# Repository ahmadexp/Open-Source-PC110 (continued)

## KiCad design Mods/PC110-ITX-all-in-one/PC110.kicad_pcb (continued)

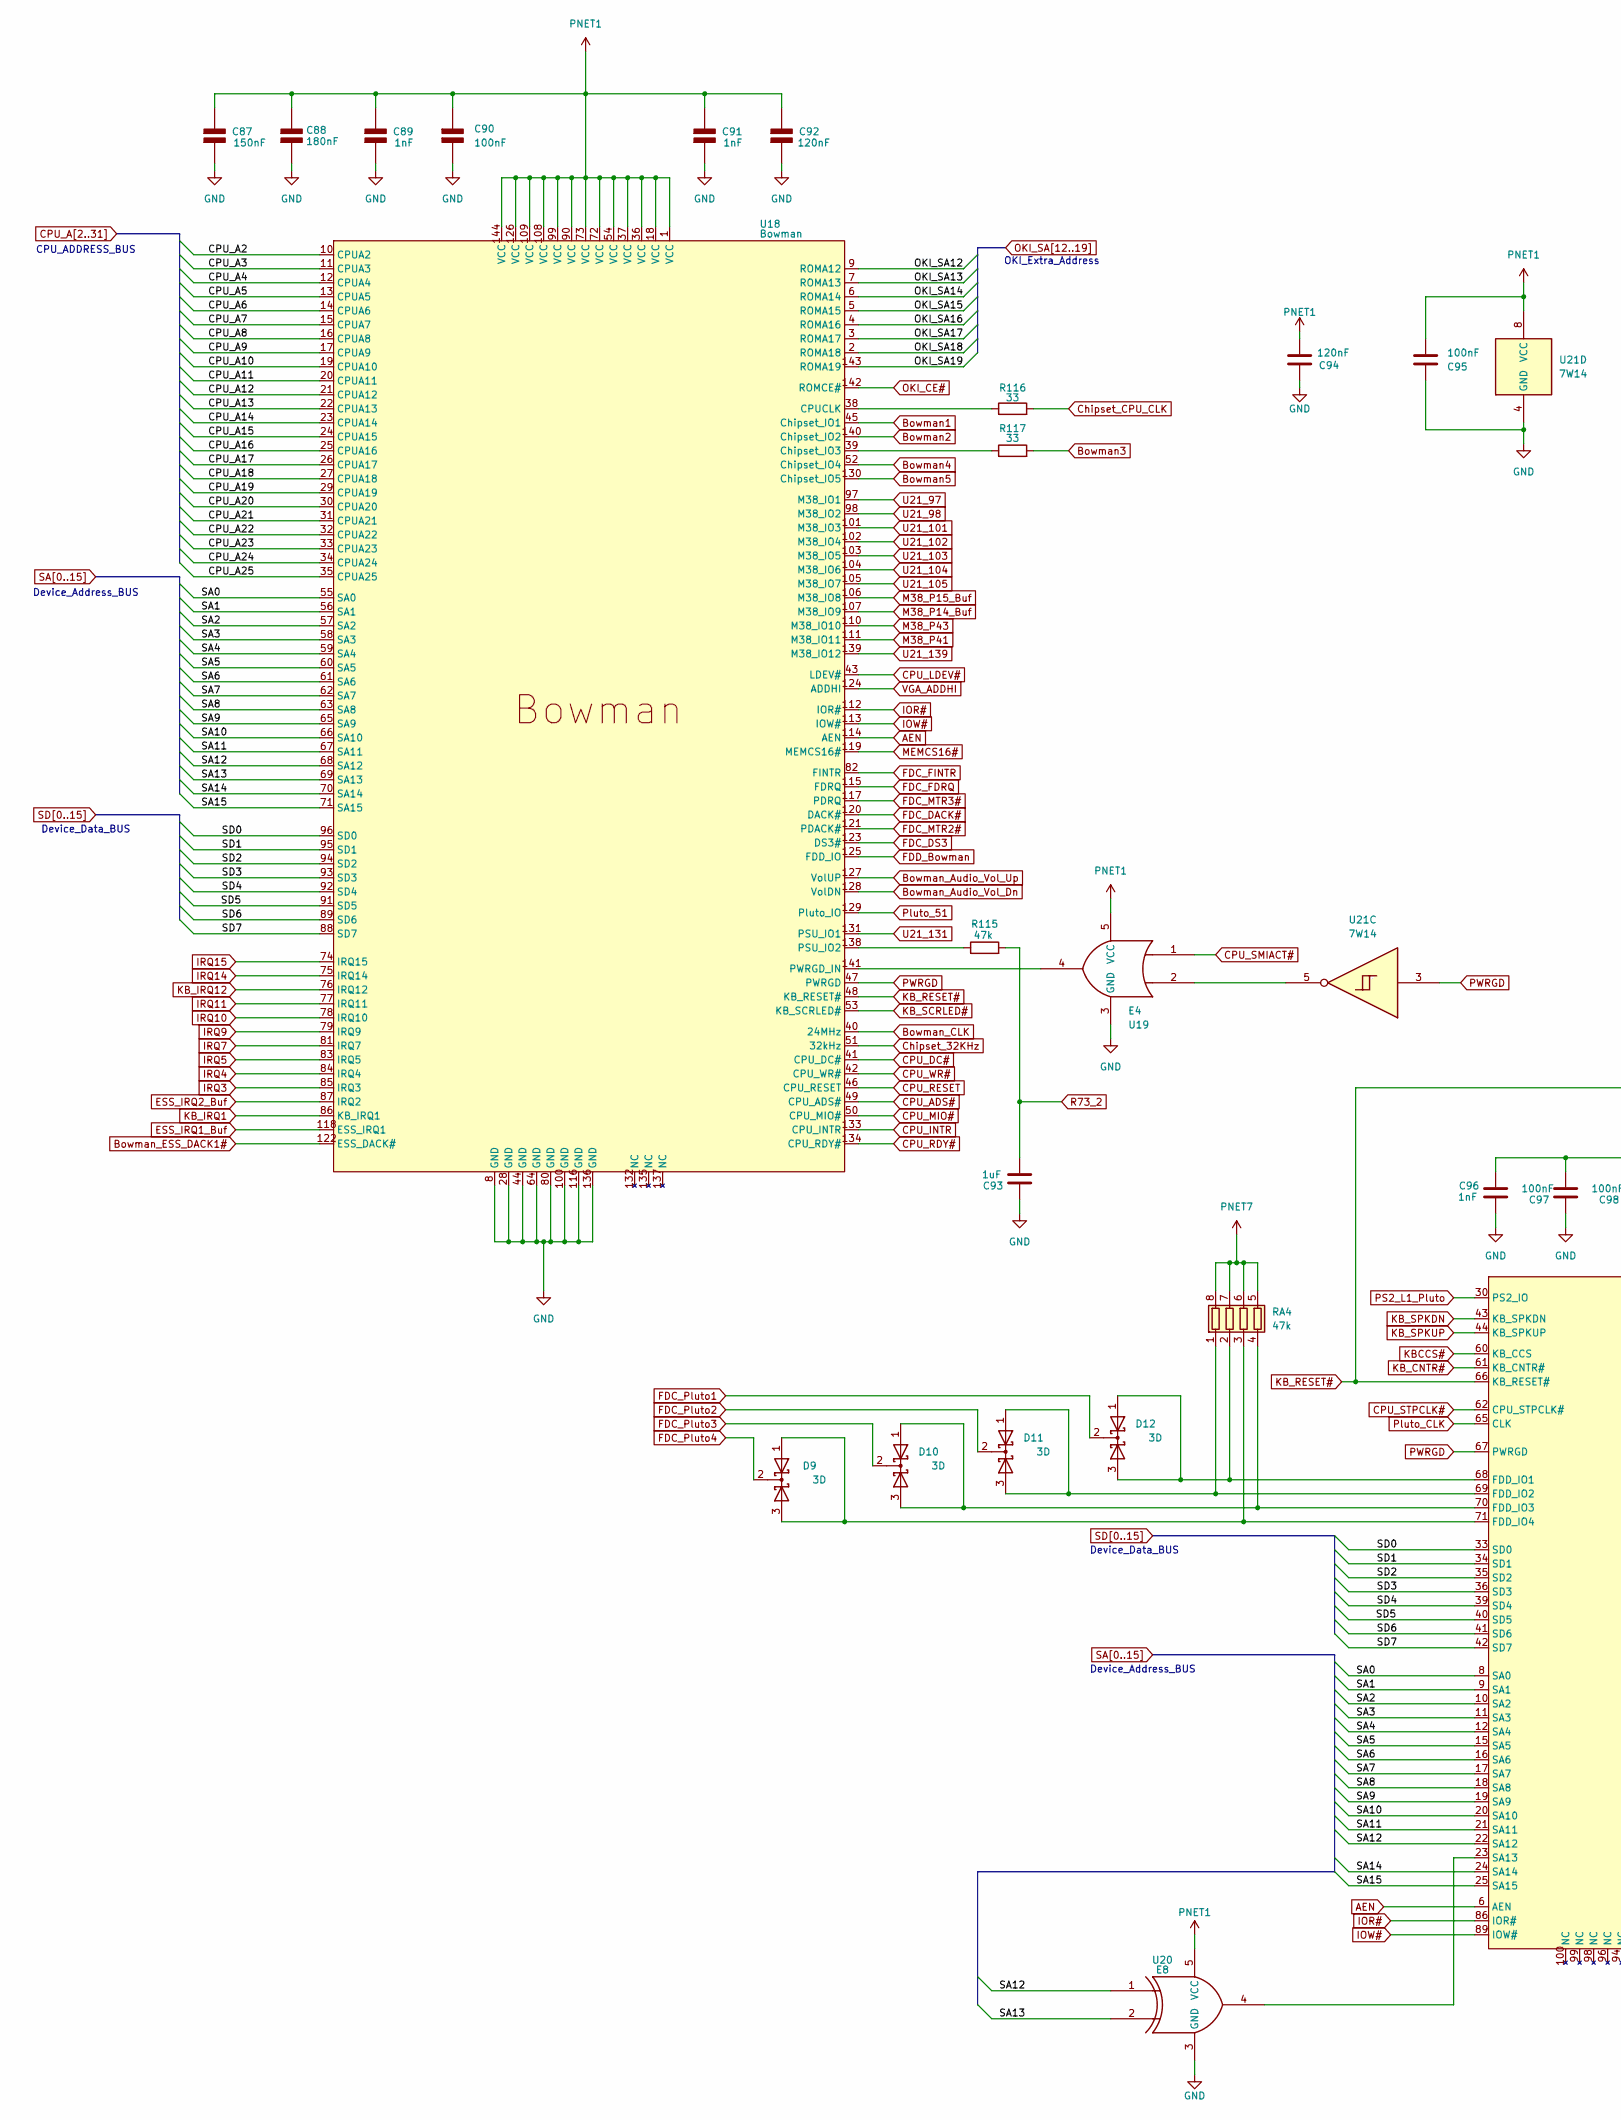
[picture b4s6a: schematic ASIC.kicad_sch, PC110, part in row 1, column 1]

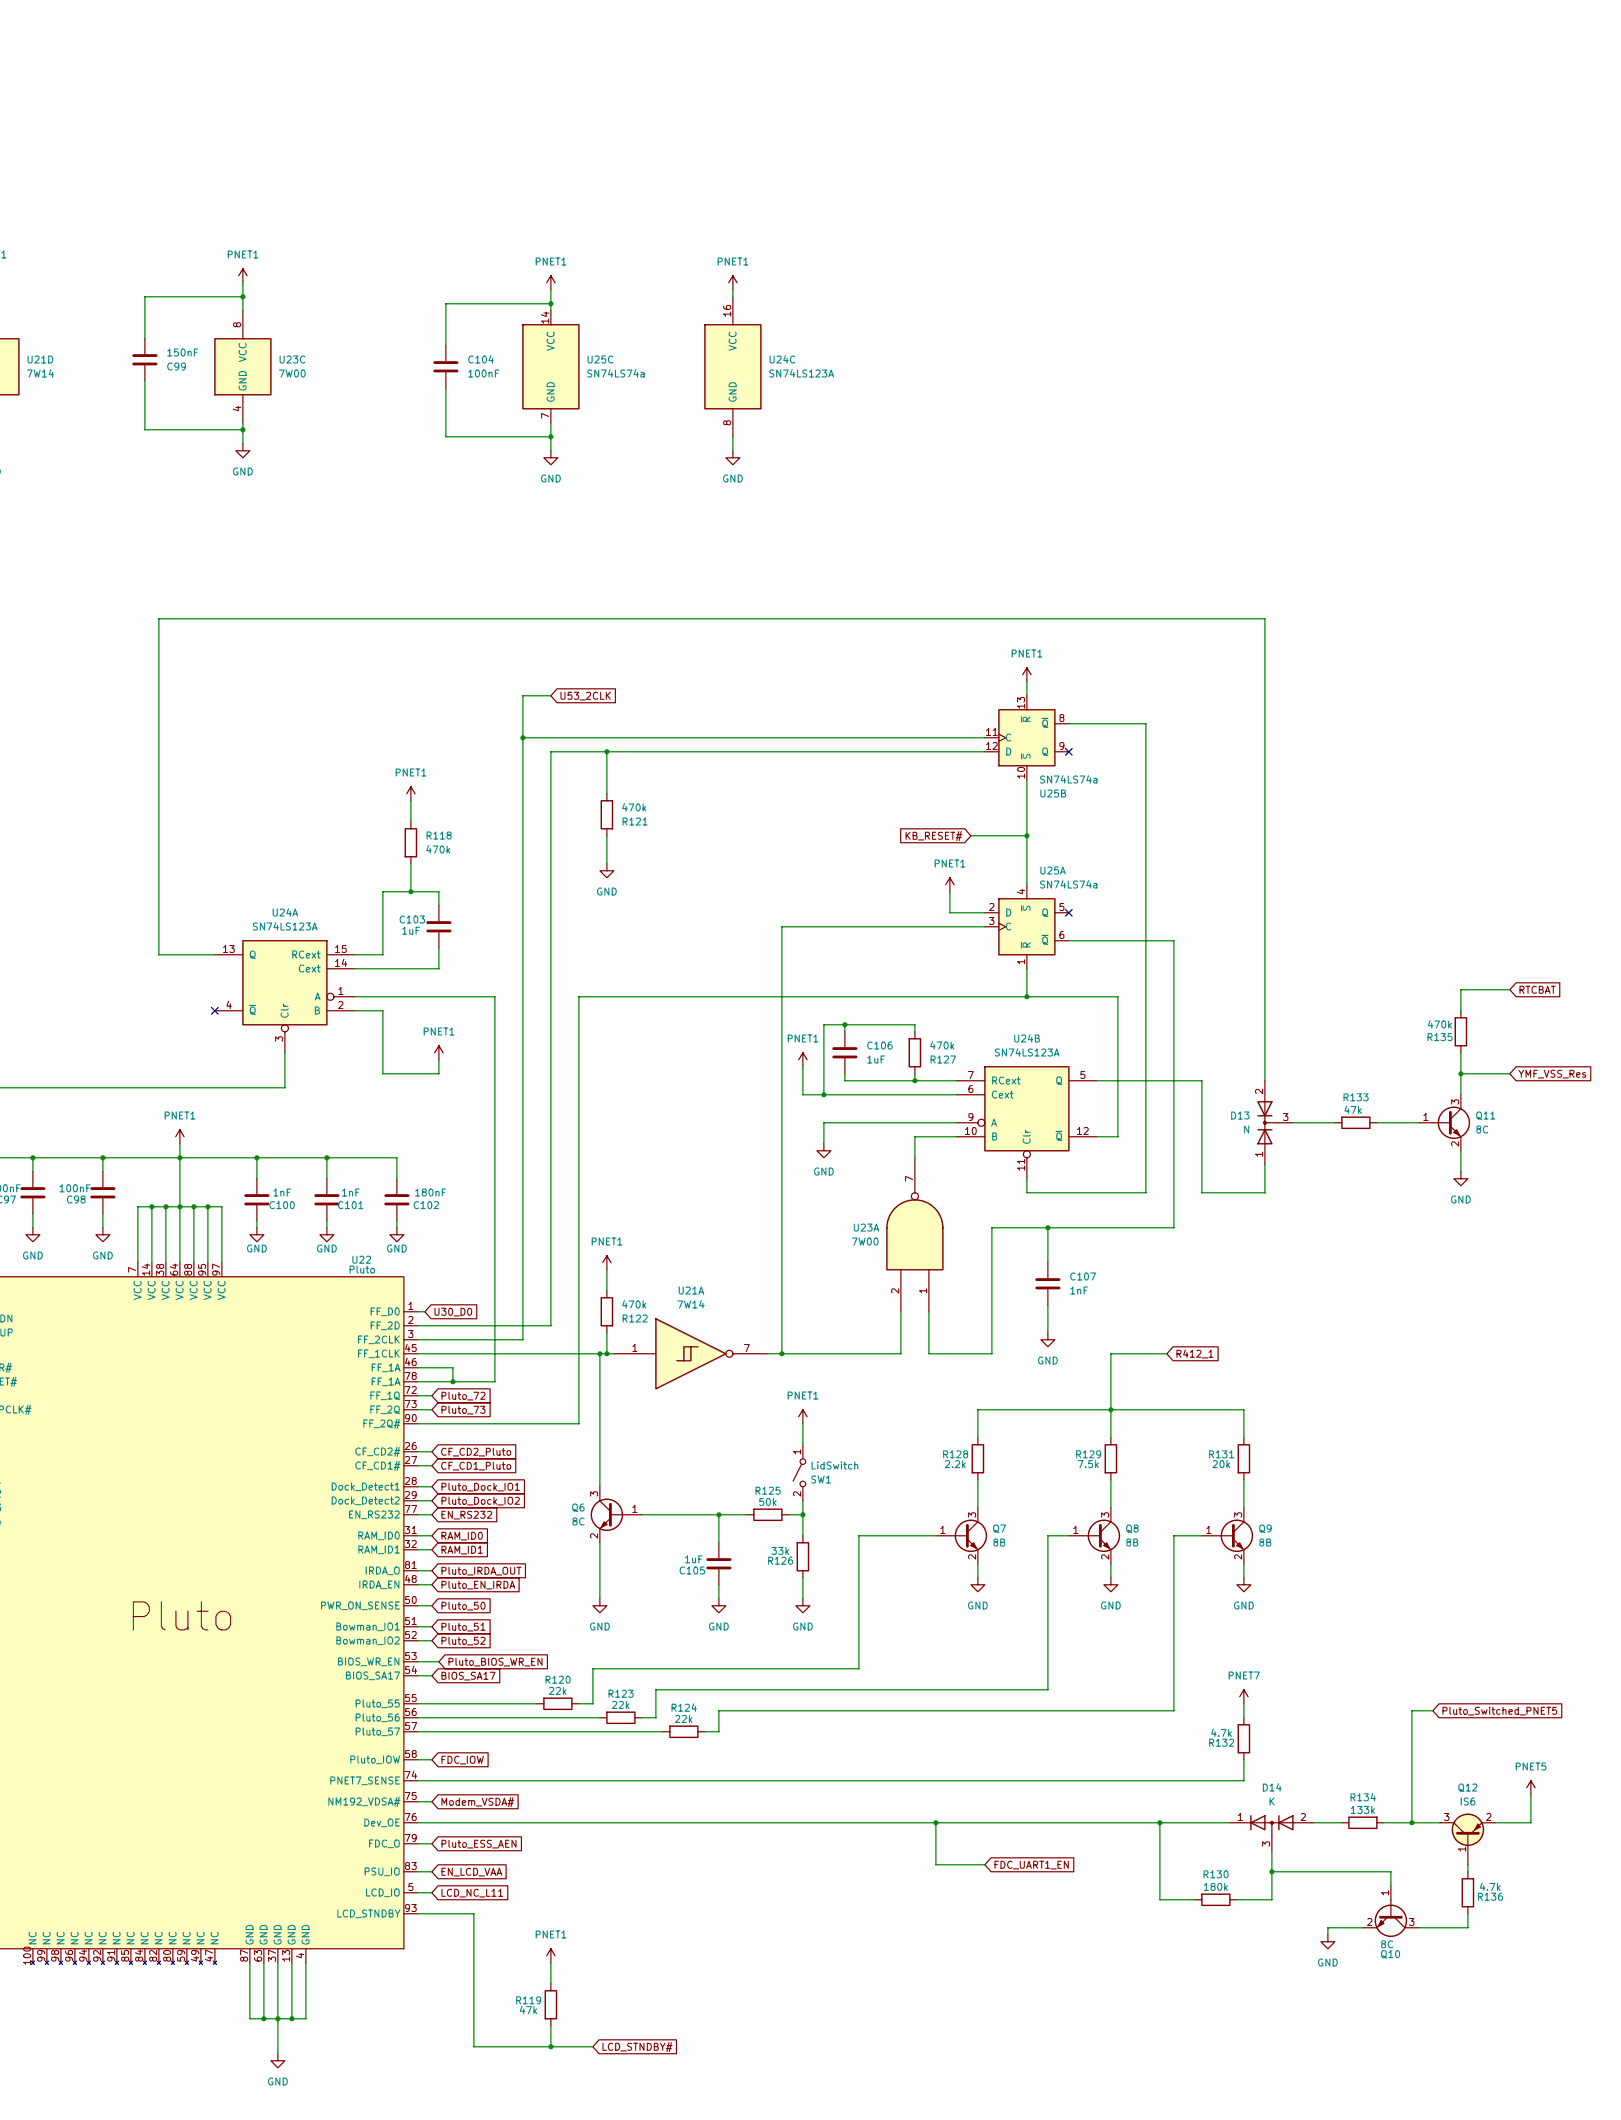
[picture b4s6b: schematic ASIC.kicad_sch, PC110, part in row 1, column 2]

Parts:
C87, C99: 150nF; C_0402_1005Metric
C88, C102: 180nF; C_0402_1005Metric
C89, C91, C96, C100, C101, C107: 1nF; C_0402_1005Metric
C90, C95, C97, C98, C104: 100nF; C_0402_1005Metric
C92, C94: 120nF; C_0402_1005Metric
C93, C103, C105, C106: 1uF; C_0603_1608Metric
D9, D10, D11, D12: 3D
D13: N; SOT-416
D14: K; SOT-416L
Q6, Q10, Q11: 8C; SOT-416
Q7, Q8: 8B; SOT-523
Q9: 8B; SOT-416
Q12: IS6; TSOT-23
R115, R119, R133: 47k; R_0402_1005Metric
R116, R117: 33; R_0402_1005Metric
R118, R121, R122, R127, R135: 470k; R_0402_1005Metric
R120, R123, R124: 22k; R_0402_1005Metric
R125: 50k; R_0402_1005Metric
R126: 33k; R_0402_1005Metric
R128: 2.2k; R_0402_1005Metric
R129: 7.5k; R_0402_1005Metric
R130: 180k; R_0402_1005Metric
R131: 20k; R_0402_1005Metric
R132, R136: 4.7k; R_0402_1005Metric
R134: 133k; R_0402_1005Metric
RA4: 47k; R-array
SW1: LidSwitch
U18: Bowman
U19: E4; SOT-353
U20: E8; SOT-353
U21: 7W14; sso-8
U22: Pluto
U23: 7W00; sso-8
U24: SN74LS123A; TSSOP-16_4.4x5mm_P0.65mm
U25: SN74LS74a; TSSOP-14_4.4x5mm_P0.65mm

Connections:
AEN: U18.114 (AEN), U22.6 (AEN); also elsewhere on the board
BIOS_SA17: U22.54 (BIOS_SA17); also elsewhere on the board
Bowman1: U18.45 (Chipset_IO1); also elsewhere on the board
Bowman2: U18.140 (Chipset_IO2); also elsewhere on the board
Bowman3: R117.2; also elsewhere on the board
Bowman4: U18.52 (Chipset_IO4); also elsewhere on the board
Bowman5: U18.130 (Chipset_IO5); also elsewhere on the board
Bowman_Audio_Vol_Dn: U18.128 (VolDN); also elsewhere on the board
Bowman_Audio_Vol_Up: U18.127 (VolUP); also elsewhere on the board
Bowman_CLK: U18.40 (24MHz); also elsewhere on the board
Bowman_ESS_DACK1#: U18.122 (ESS_DACK#); also elsewhere on the board
CF_CD1_Pluto: U22.27 (CF_CD1#); also elsewhere on the board
CF_CD2_Pluto: U22.26 (CF_CD2#); also elsewhere on the board
CPU_A2: U18.10 (CPUA2); also elsewhere on the board
CPU_A3: U18.11 (CPUA3); also elsewhere on the board
CPU_A4: U18.12 (CPUA4); also elsewhere on the board
CPU_A5: U18.13 (CPUA5); also elsewhere on the board
CPU_A6: U18.14 (CPUA6); also elsewhere on the board
CPU_A7: U18.15 (CPUA7); also elsewhere on the board
CPU_A8: U18.16 (CPUA8); also elsewhere on the board
CPU_A9: U18.17 (CPUA9); also elsewhere on the board
CPU_A10: U18.19 (CPUA10); also elsewhere on the board
CPU_A11: U18.20 (CPUA11); also elsewhere on the board
CPU_A12: U18.21 (CPUA12); also elsewhere on the board
CPU_A13: U18.22 (CPUA13); also elsewhere on the board
CPU_A14: U18.23 (CPUA14); also elsewhere on the board
CPU_A15: U18.24 (CPUA15); also elsewhere on the board
CPU_A16: U18.25 (CPUA16); also elsewhere on the board
CPU_A17: U18.26 (CPUA17); also elsewhere on the board
CPU_A18: U18.27 (CPUA18); also elsewhere on the board
CPU_A19: U18.29 (CPUA19); also elsewhere on the board
CPU_A20: U18.30 (CPUA20); also elsewhere on the board
CPU_A21: U18.31 (CPUA21); also elsewhere on the board
CPU_A22: U18.32 (CPUA22); also elsewhere on the board
CPU_A23: U18.33 (CPUA23); also elsewhere on the board
CPU_A24: U18.34 (CPUA24); also elsewhere on the board
CPU_A25: U18.35 (CPUA25); also elsewhere on the board
CPU_ADS#: U18.49 (CPU_ADS#); also elsewhere on the board
CPU_DC#: U18.41 (CPU_DC#); also elsewhere on the board
CPU_INTR: U18.133 (CPU_INTR); also elsewhere on the board
CPU_LDEV#: U18.43 (LDEV#); also elsewhere on the board
CPU_MIO#: U18.50 (CPU_MIO#); also elsewhere on the board
CPU_RDY#: U18.134 (CPU_RDY#); also elsewhere on the board
CPU_RESET: U18.46 (CPU_RESET); also elsewhere on the board
CPU_SMIACT#: U19.1; also elsewhere on the board
CPU_STPCLK#: U22.62 (CPU_STPCLK#); also elsewhere on the board
CPU_WR#: U18.42 (CPU_WR#); also elsewhere on the board
Chipset_32KHz: U18.51 (32kHz); also elsewhere on the board
Chipset_CPU_CLK: R116.2; also elsewhere on the board
EN_LCD_VAA: U22.83 (PSU_IO); also elsewhere on the board
EN_RS232: U22.77 (EN_RS232); also elsewhere on the board
ESS_IRQ1_Buf: U18.118 (ESS_IRQ1); also elsewhere on the board
ESS_IRQ2_Buf: U18.87 (IRQ2); also elsewhere on the board
FDC_DACK#: U18.120 (DACK#); also elsewhere on the board
FDC_DS3: U18.123 (DS3#); also elsewhere on the board
FDC_FDRQ: U18.115 (FDRQ); also elsewhere on the board
FDC_FINTR: U18.82 (FINTR); also elsewhere on the board
FDC_IOW: U22.58 (Pluto_IOW); also elsewhere on the board
FDC_MTR2#: U18.121 (PDACK#); also elsewhere on the board
FDC_MTR3#: U18.117 (PDRQ); also elsewhere on the board
FDC_Pluto1: D12.2 (K); also elsewhere on the board
FDC_Pluto2: D11.2 (K); also elsewhere on the board
FDC_Pluto3: D10.2 (K); also elsewhere on the board
FDC_Pluto4: D9.2 (K); also elsewhere on the board
FDC_UART1_EN: D14.1 (K), R130.2, U22.76 (Dev_OE); also elsewhere on the board
FDD_Bowman: U18.125 (FDD_IO); also elsewhere on the board
GND: C87.1 (+), C88.1 (+), C89.1 (+), C90.2 (-), C91.1 (+), C92.1 (+), C93.1, C94.1, C95.2, C96.2, C97.1, C98.1, C99.2, C100.1, C101.1, C102.1, C104.1, C105.1, C107.1, Q6.2 (E), Q7.2 (E), Q8.2 (E), Q9.2 (E), Q10.2 (E), Q11.2 (E), R121.2, R126.1, U18.8 (GND), U18.28 (GND), U18.44 (GND), U18.64 (GND), U18.80 (GND), U18.100 (GND), U18.116 (GND), U18.136 (GND), U19.3 (GND), U20.3 (GND), U21.4 (GND), U22.4 (GND), U22.13 (GND), U22.37 (GND), U22.63 (GND), U22.87 (GND), U23.4 (GND), U24.8 (GND), U24.9 (A), U25.7 (GND); also elsewhere on the board
IOR#: U18.112 (IOR#), U22.86 (IOR#); also elsewhere on the board
IOW#: U18.113 (IOW#), U22.89 (IOW#); also elsewhere on the board
IRQ3: U18.85 (IRQ3); also elsewhere on the board
IRQ4: U18.84 (IRQ4); also elsewhere on the board
IRQ5: U18.83 (IRQ5); also elsewhere on the board
IRQ7: U18.81 (IRQ7); also elsewhere on the board
IRQ9: U18.79 (IRQ9); also elsewhere on the board
IRQ10: U18.78 (IRQ10); also elsewhere on the board
IRQ11: U18.77 (IRQ11); also elsewhere on the board
IRQ14: U18.75 (IRQ14); also elsewhere on the board
IRQ15: U18.74 (IRQ15); also elsewhere on the board
KBCCS#: U22.60 (KB_CCS); also elsewhere on the board
KB_CNTR#: U22.61 (KB_CNTR#); also elsewhere on the board
KB_IRQ1: U18.86 (KB_IRQ1); also elsewhere on the board
KB_IRQ12: U18.76 (IRQ12); also elsewhere on the board
KB_RESET#: U18.48 (KB_RESET#), U22.66 (KB_RESET#), U24.3 (Clr), U25.4 (~S), U25.10 (~S); also elsewhere on the board
KB_SCRLED#: U18.53 (KB_SCRLED#); also elsewhere on the board
KB_SPKDN: U22.43 (KB_SPKDN); also elsewhere on the board
KB_SPKUP: U22.44 (KB_SPKUP); also elsewhere on the board
LCD_NC_L11: U22.5 (LCD_IO); also elsewhere on the board
LCD_STNDBY#: R119.2, U22.93 (LCD_STNDBY); also elsewhere on the board
M38_P14_Buf: U18.107 (M38_IO9); also elsewhere on the board
M38_P15_Buf: U18.106 (M38_IO8); also elsewhere on the board
M38_P41: U18.111 (M38_IO11); also elsewhere on the board
M38_P43: U18.110 (M38_IO10); also elsewhere on the board
MEMCS16#: U18.119 (MEMCS16#); also elsewhere on the board
Modem_VSDA#: U22.75 (NM192_VDSA#); also elsewhere on the board
unnamed: D13.3, R133.2
unnamed: D14.2 (A), R134.1
unnamed: D14.3 (common), Q10.1 (B), R130.1
unnamed: C105.2, Q6.1 (B), R125.2
unnamed: Q6.3 (C), R122.2, U21.1, U22.45 (FF_1CLK)
unnamed: Q7.1 (B), R120.1
unnamed: Q7.3 (C), R128.2
unnamed: Q8.1 (B), R123.1
unnamed: Q8.3 (C), R129.2
unnamed: Q9.1 (B), R124.1
unnamed: Q9.3 (C), R131.2
unnamed: Q10.3 (C), R136.1
unnamed: Q11.1 (B), R133.1
unnamed: Q12.1 (B), R136.2
unnamed: D11.1 (A), D11.3 (A), RA4.1 (R1.1), U22.69 (FDD_IO2)
unnamed: D12.1 (A), D12.3 (A), RA4.2 (R2.1), U22.68 (FDD_IO1)
unnamed: D9.1 (A), D9.3 (A), RA4.3 (R3.1), U22.71 (FDD_IO4)
unnamed: D10.1 (A), D10.3 (A), RA4.4 (R4.1), U22.70 (FDD_IO3)
unnamed: R125.1, R126.2, SW1.2 (B)
unnamed: R116.1, U18.38 (CPUCLK)
unnamed: R117.1, U18.39 (Chipset_IO3)
unnamed: R115.1, U18.138 (PSU_IO2)
unnamed: U18.141 (PWRGD_IN), U19.4
unnamed: U19.2, U21.5
unnamed: R121.1, U22.2 (FF_2D), U25.12 (D)
unnamed: U22.90 (FF_2Q#), U24.12 (~Q), U25.1 (~R)
unnamed: R132.1, U22.74 (PNET7_SENSE)
unnamed: R120.2, U22.55 (Pluto_55)
unnamed: R123.2, U22.56 (Pluto_56)
unnamed: R124.2, U22.57 (Pluto_57)
unnamed: U20.4, U22.23 (SA13)
unnamed: U22.46 (FF_1A), U22.78 (FF_1A), U24.1 (A)
unnamed: C103.2, U24.14 (Cext)
unnamed: D13.2, U24.13 (Q)
unnamed: C103.1, R118.2, U24.15 (RCext)
unnamed: U23.7, U24.10 (B)
unnamed: U24.11 (Clr), U25.8 (~Q)
unnamed: D13.1, U24.5 (Q)
unnamed: C106.1, R127.1, U24.7 (RCext)
unnamed: U21.7, U23.2, U25.3 (C)
unnamed: C107.2, U23.1, U25.6 (~Q)
OKI_CE#: U18.142 (ROMCE#); also elsewhere on the board
OKI_SA12: U18.9 (ROMA12); also elsewhere on the board
OKI_SA13: U18.7 (ROMA13); also elsewhere on the board
OKI_SA14: U18.6 (ROMA14); also elsewhere on the board
OKI_SA15: U18.5 (ROMA15); also elsewhere on the board
OKI_SA16: U18.4 (ROMA16); also elsewhere on the board
OKI_SA17: U18.3 (ROMA17); also elsewhere on the board
OKI_SA18: U18.2 (ROMA18); also elsewhere on the board
OKI_SA19: U18.143 (ROMA19); also elsewhere on the board
PNET1: C87.2 (-), C88.2 (-), C89.2 (-), C90.1 (+), C91.2 (-), C92.2 (-), C94.2, C95.1, C96.1, C97.2, C98.2, C99.1, C100.2, C101.2, C102.2, C104.2, C106.2, R118.1, R119.1, R122.1, R127.2, SW1.1 (A), U18.1 (VCC), U18.18 (VCC), U18.36 (VCC), U18.37 (VCC), U18.54 (VCC), U18.72 (VCC), U18.73 (VCC), U18.90 (VCC), U18.99 (VCC), U18.108 (VCC), U18.109 (VCC), U18.126 (VCC), U18.144 (VCC), U19.5 (VCC), U20.5 (VCC), U21.8 (VCC), U22.7 (VCC), U22.14 (VCC), U22.38 (VCC), U22.64 (VCC), U22.88 (VCC), U22.95 (VCC), U22.97 (VCC), U23.8 (VCC), U24.2 (B), U24.6 (Cext), U24.16 (VCC), U25.2 (D), U25.13 (~R), U25.14 (VCC); also elsewhere on the board
PNET5: Q12.2 (E); also elsewhere on the board
PNET7: R132.2, RA4.5 (R4.2), RA4.6 (R3.2), RA4.7 (R2.2), RA4.8 (R1.2); also elsewhere on the board
PS2_L1_Pluto: U22.30 (PS2_IO); also elsewhere on the board
PWRGD: U18.47 (PWRGD), U21.3, U22.67 (PWRGD); also elsewhere on the board
Pluto_50: U22.50 (PWR_ON_SENSE); also elsewhere on the board
Pluto_51: U18.129 (Pluto_IO), U22.51 (Bowman_IO1)
Pluto_52: U22.52 (Bowman_IO2); also elsewhere on the board
Pluto_72: U22.72 (FF_1Q); also elsewhere on the board
Pluto_73: U22.73 (FF_2Q); also elsewhere on the board
Pluto_BIOS_WR_EN: U22.53 (BIOS_WR_EN); also elsewhere on the board
Pluto_CLK: U22.65 (CLK); also elsewhere on the board
Pluto_Dock_IO1: U22.28 (Dock_Detect1); also elsewhere on the board
Pluto_Dock_IO2: U22.29 (Dock_Detect2); also elsewhere on the board
Pluto_EN_IRDA: U22.48 (IRDA_EN); also elsewhere on the board
Pluto_ESS_AEN: U22.79 (FDC_O); also elsewhere on the board
Pluto_IRDA_OUT: U22.81 (IRDA_O); also elsewhere on the board
Pluto_Switched_PNET5: Q12.3 (C), R134.2; also elsewhere on the board
R73_2: C93.2, R115.2; also elsewhere on the board
R412_1: R128.1, R129.1, R131.1; also elsewhere on the board
RAM_ID0: U22.31 (RAM_ID0); also elsewhere on the board
RAM_ID1: U22.32 (RAM_ID1); also elsewhere on the board
RTCBAT: R135.2; also elsewhere on the board
SA0: U18.55 (SA0), U22.8 (SA0); also elsewhere on the board
SA1: U18.56 (SA1), U22.9 (SA1); also elsewhere on the board
SA2: U18.57 (SA2), U22.10 (SA2); also elsewhere on the board
SA3: U18.58 (SA3), U22.11 (SA3); also elsewhere on the board
SA4: U18.59 (SA4), U22.12 (SA4); also elsewhere on the board
SA5: U18.60 (SA5), U22.15 (SA5); also elsewhere on the board
SA6: U18.61 (SA6), U22.16 (SA6); also elsewhere on the board
SA7: U18.62 (SA7), U22.17 (SA7); also elsewhere on the board
SA8: U18.63 (SA8), U22.18 (SA8); also elsewhere on the board
SA9: U18.65 (SA9), U22.19 (SA9); also elsewhere on the board
SA10: U18.66 (SA10), U22.20 (SA10); also elsewhere on the board
SA11: U18.67 (SA11), U22.21 (SA11); also elsewhere on the board
SA12: U18.68 (SA12), U20.1, U22.22 (SA12); also elsewhere on the board
SA13: U18.69 (SA13), U20.2; also elsewhere on the board
SA14: U18.70 (SA14), U22.24 (SA14); also elsewhere on the board
SA15: U18.71 (SA15), U22.25 (SA15); also elsewhere on the board
SD0: U18.96 (SD0), U22.33 (SD0); also elsewhere on the board
SD1: U18.95 (SD1), U22.34 (SD1); also elsewhere on the board
SD2: U18.94 (SD2), U22.35 (SD2); also elsewhere on the board
SD3: U18.93 (SD3), U22.36 (SD3); also elsewhere on the board
SD4: U18.92 (SD4), U22.39 (SD4); also elsewhere on the board
SD5: U18.91 (SD5), U22.40 (SD5); also elsewhere on the board
SD6: U18.89 (SD6), U22.41 (SD6); also elsewhere on the board
SD7: U18.88 (SD7), U22.42 (SD7); also elsewhere on the board
U21_97: U18.97 (M38_IO1); also elsewhere on the board
U21_98: U18.98 (M38_IO2); also elsewhere on the board
U21_101: U18.101 (M38_IO3); also elsewhere on the board
U21_102: U18.102 (M38_IO4); also elsewhere on the board
U21_103: U18.103 (M38_IO5); also elsewhere on the board
U21_104: U18.104 (M38_IO6); also elsewhere on the board
U21_105: U18.105 (M38_IO7); also elsewhere on the board
U21_131: U18.131 (PSU_IO1); also elsewhere on the board
U21_139: U18.139 (M38_IO12); also elsewhere on the board
U30_D0: U22.1 (FF_D0); also elsewhere on the board
U53_2CLK: U22.3 (FF_2CLK), U25.11 (C); also elsewhere on the board
VGA_ADDHI: U18.124 (ADDHI); also elsewhere on the board
YMF_VSS_Res: Q11.3 (C), R135.1; also elsewhere on the board

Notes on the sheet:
OKI_Extra_Address
CPU_ADDRESS_BUS
Device_Data_BUS
Device_Address_BUS

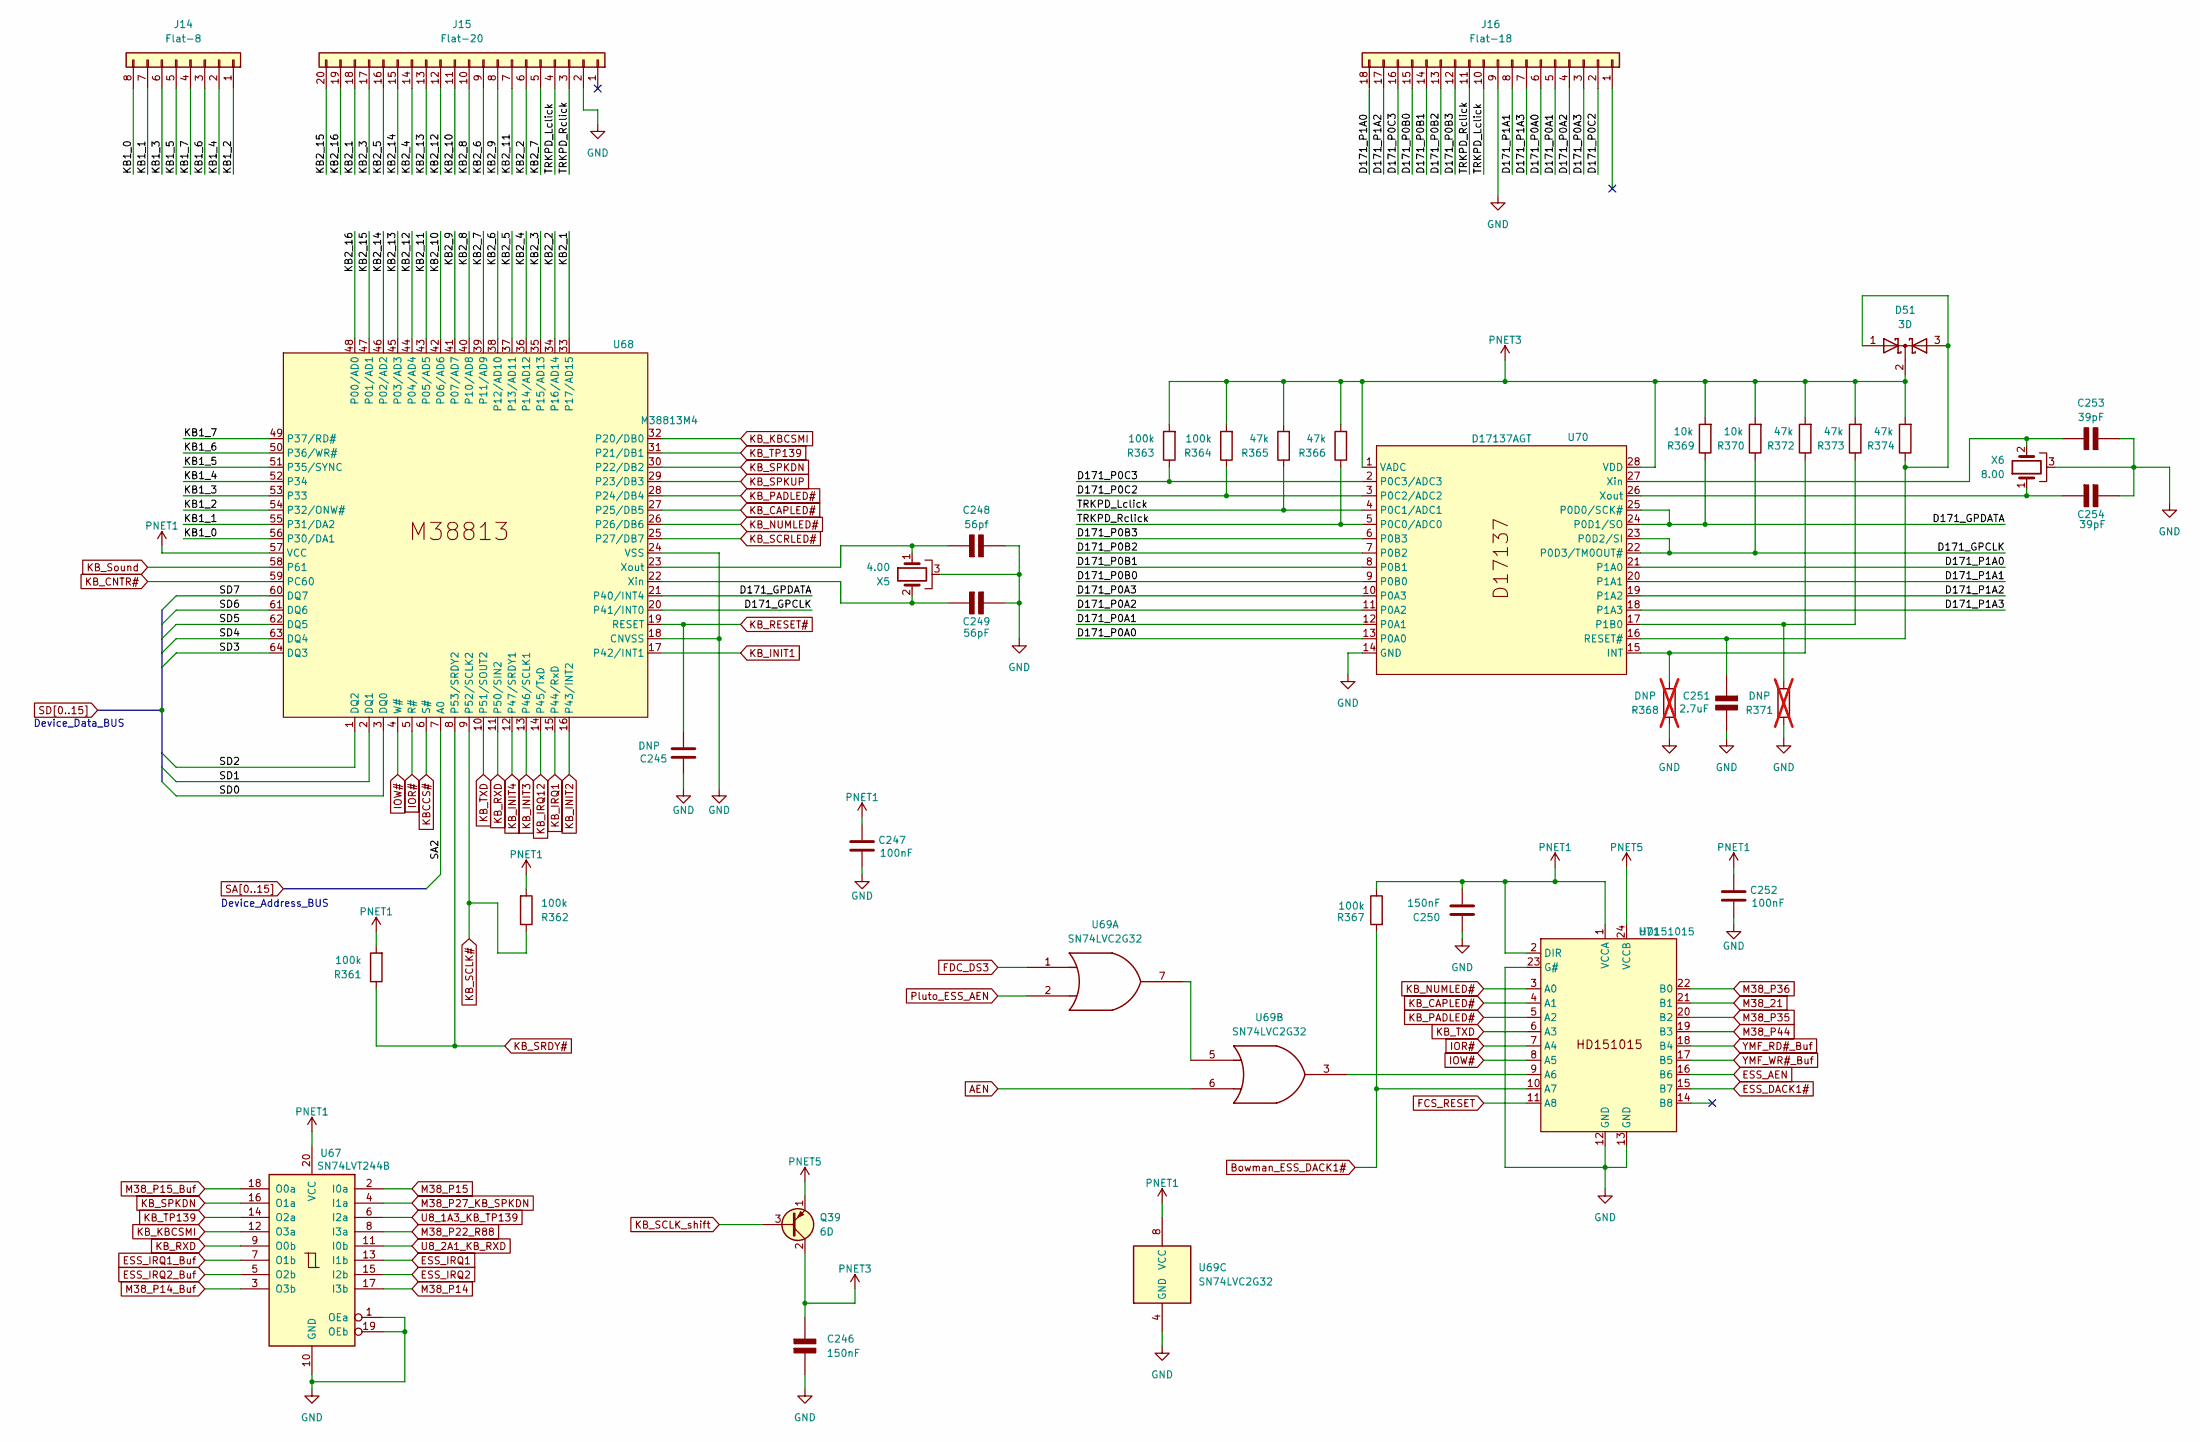
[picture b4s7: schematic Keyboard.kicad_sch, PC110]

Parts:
C245: DNP; C_0402_1005Metric
C246, C250: 150nF; C_0402_1005Metric
C247, C252: 100nF; C_0402_1005Metric
C248: 56pf; C_0402_1005Metric
C249: 56pF; C_0402_1005Metric
C251: 2.7uF; C_0805_2012Metric
C253, C254: 39pF; C_0402_1005Metric
D51: 3D
J14: Flat-8
J15: Flat-20
J16: Flat-18
Q39: 6D; 3D
R361, R362, R363, R364, R367: 100k; R_0402_1005Metric
R365, R366, R372, R373, R374: 47k; R_0402_1005Metric
R368, R371: DNP; R_0402_1005Metric; not fitted
R369, R370: 10k; R_0402_1005Metric
U67: SN74LVT244B; TSSOP-20_4.4x6.5mm_P0.65mm
U68: M38813M4; QFN64
U69: SN74LVC2G32; SSOP-8_2.95x2.8mm_P0.65mm
U70: D17137AGT; SSOP-28
U71: HD151015; SSOP-24_5.3x8.2mm_P0.65mm
X5: 4.00; XTAL-5
X6: 8.00; XTAL-4

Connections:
/Keyboard and Trackpoint/D171_GPCLK: R370.1, U68.20 (P41/INT0), U70.22 (P0D3/TM0OUT#), U70.23 (P0D2/SI)
/Keyboard and Trackpoint/D171_GPDATA: R369.1, U68.21 (P40/INT4), U70.24 (P0D1/SO), U70.25 (P0D0/SCK#)
/Keyboard and Trackpoint/D171_P0A0: J16.6, U70.13 (P0A0)
/Keyboard and Trackpoint/D171_P0A1: J16.5, U70.12 (P0A1)
/Keyboard and Trackpoint/D171_P0A2: J16.4, U70.11 (P0A2)
/Keyboard and Trackpoint/D171_P0A3: J16.3, U70.10 (P0A3)
/Keyboard and Trackpoint/D171_P0B0: J16.15, U70.9 (P0B0)
/Keyboard and Trackpoint/D171_P0B1: J16.14, U70.8 (P0B1)
/Keyboard and Trackpoint/D171_P0B2: J16.13, U70.7 (P0B2)
/Keyboard and Trackpoint/D171_P0B3: J16.12, U70.6 (P0B3)
/Keyboard and Trackpoint/D171_P0C2: J16.2, R364.1, U70.3 (P0C2/ADC2)
/Keyboard and Trackpoint/D171_P0C3: J16.16, R363.1, U70.2 (P0C3/ADC3)
/Keyboard and Trackpoint/D171_P1A0: J16.18, U70.21 (P1A0)
/Keyboard and Trackpoint/D171_P1A1: J16.8, U70.20 (P1A1)
/Keyboard and Trackpoint/D171_P1A2: J16.17, U70.19 (P1A2)
/Keyboard and Trackpoint/D171_P1A3: J16.7, U70.18 (P1A3)
/Keyboard and Trackpoint/KB1_0: J14.8, U68.56 (P30/DA1)
/Keyboard and Trackpoint/KB1_1: J14.7, U68.55 (P31/DA2)
/Keyboard and Trackpoint/KB1_2: J14.1, U68.54 (P32/ONW#)
/Keyboard and Trackpoint/KB1_3: J14.6, U68.53 (P33)
/Keyboard and Trackpoint/KB1_4: J14.2, U68.52 (P34)
/Keyboard and Trackpoint/KB1_5: J14.5, U68.51 (P35/SYNC)
/Keyboard and Trackpoint/KB1_6: J14.3, U68.50 (P36/WR#)
/Keyboard and Trackpoint/KB1_7: J14.4, U68.49 (P37/RD#)
/Keyboard and Trackpoint/KB2_1: J15.18, U68.33 (P17/AD15)
/Keyboard and Trackpoint/KB2_2: J15.6, U68.34 (P16/AD14)
/Keyboard and Trackpoint/KB2_3: J15.17, U68.35 (P15/AD13)
/Keyboard and Trackpoint/KB2_4: J15.14, U68.36 (P14/AD12)
/Keyboard and Trackpoint/KB2_5: J15.16, U68.37 (P13/AD11)
/Keyboard and Trackpoint/KB2_6: J15.9, U68.38 (P12/AD10)
/Keyboard and Trackpoint/KB2_7: J15.5, U68.39 (P11/AD9)
/Keyboard and Trackpoint/KB2_8: J15.10, U68.40 (P10/AD8)
/Keyboard and Trackpoint/KB2_9: J15.8, U68.41 (P07/AD7)
/Keyboard and Trackpoint/KB2_10: J15.11, U68.42 (P06/AD6)
/Keyboard and Trackpoint/KB2_11: J15.7, U68.43 (P05/AD5)
/Keyboard and Trackpoint/KB2_12: J15.12, U68.44 (P04/AD4)
/Keyboard and Trackpoint/KB2_13: J15.13, U68.45 (P03/AD3)
/Keyboard and Trackpoint/KB2_14: J15.15, U68.46 (P02/AD2)
/Keyboard and Trackpoint/KB2_15: J15.20, U68.47 (P01/AD1)
/Keyboard and Trackpoint/KB2_16: J15.19, U68.48 (P00/AD0)
/Keyboard and Trackpoint/TRKPD_Lclick: J15.4, J16.10, R365.1, U70.4 (P0C1/ADC1)
/Keyboard and Trackpoint/TRKPD_Rclick: J15.3, J16.11, R366.1, U70.5 (P0C0/ADC0)
AEN: U69.6; also elsewhere on the board
Bowman_ESS_DACK1#: R367.2, U71.10 (A7); also elsewhere on the board
ESS_AEN: U71.16 (B6); also elsewhere on the board
ESS_DACK1#: U71.15 (B7); also elsewhere on the board
ESS_IRQ1: U67.13 (I1b); also elsewhere on the board
ESS_IRQ1_Buf: U67.7 (O1b); also elsewhere on the board
ESS_IRQ2: U67.15 (I2b); also elsewhere on the board
ESS_IRQ2_Buf: U67.5 (O2b); also elsewhere on the board
FCS_RESET: U71.11 (A8); also elsewhere on the board
FDC_DS3: U69.1; also elsewhere on the board
GND: C245.1, C246.2 (-), C247.2, C248.1 (+), C249.1 (+), C250.2, C251.2 (-), C252.2, C253.1 (+), C254.2 (-), J15.2, J16.9, R368.1, R371.1, U67.1 (OEa), U67.10 (GND), U67.19 (OEb), U68.18 (CNVSS), U68.24 (VSS), U69.4 (GND), U70.14 (GND), U71.12 (GND), U71.13 (GND), U71.23 (G#), X5.3, X6.3; also elsewhere on the board
IOR#: U68.5 (R#), U71.7 (A4); also elsewhere on the board
IOW#: U68.4 (W#), U71.8 (A5); also elsewhere on the board
KBCCS#: U68.6 (S#); also elsewhere on the board
KB_CAPLED#: U68.27 (P25/DB5), U71.4 (A1)
KB_CNTR#: U68.59 (PC60); also elsewhere on the board
KB_INIT1: U68.17 (P42/INT1); also elsewhere on the board
KB_INIT2: U68.16 (P43/INT2); also elsewhere on the board
KB_INIT3: U68.13 (P46/SCLK1); also elsewhere on the board
KB_INIT4: U68.12 (P47/SRDY1); also elsewhere on the board
KB_IRQ1: U68.15 (P44/RxD); also elsewhere on the board
KB_IRQ12: U68.14 (P45/TxD); also elsewhere on the board
KB_KBCSMI: U67.12 (O3a), U68.32 (P20/DB0)
KB_NUMLED#: U68.26 (P26/DB6), U71.3 (A0)
KB_PADLED#: U68.28 (P24/DB4), U71.5 (A2)
KB_RESET#: C245.2, U68.19 (RESET); also elsewhere on the board
KB_RXD: U67.9 (O0b), U68.11 (P50/SIN2)
KB_SCLK#: R362.1, U68.9 (P52/SCLK2); also elsewhere on the board
KB_SCLK_shift: Q39.3 (B); also elsewhere on the board
KB_SCRLED#: U68.25 (P27/DB7); also elsewhere on the board
KB_SPKDN: U67.16 (O1a), U68.30 (P22/DB2); also elsewhere on the board
KB_SPKUP: U68.29 (P23/DB3); also elsewhere on the board
KB_SRDY#: R361.1, U68.8 (P53/SRDY2); also elsewhere on the board
KB_Sound: U68.58 (P61); also elsewhere on the board
KB_TP139: U67.14 (O2a), U68.31 (P21/DB1)
KB_TXD: U68.10 (P51/SOUT2), U71.6 (A3)
M38_21: U71.21 (B1); also elsewhere on the board
M38_P14: U67.17 (I3b); also elsewhere on the board
M38_P14_Buf: U67.3 (O3b); also elsewhere on the board
M38_P15: U67.2 (I0a); also elsewhere on the board
M38_P15_Buf: U67.18 (O0a); also elsewhere on the board
M38_P22_R88: U67.8 (I3a); also elsewhere on the board
M38_P27_KB_SPKDN: U67.4 (I1a); also elsewhere on the board
M38_P35: U71.20 (B2); also elsewhere on the board
M38_P36: U71.22 (B0); also elsewhere on the board
M38_P44: U71.19 (B3); also elsewhere on the board
unnamed: C248.2 (-), U68.23 (Xout), X5.1
unnamed: C249.2 (-), U68.22 (Xin), X5.2
unnamed: C251.1 (+), D51.1 (A), D51.3 (A), R374.1, U70.16 (RESET#)
unnamed: C253.2 (-), U70.27 (Xin), X6.2
unnamed: C254.1 (+), U70.26 (Xout), X6.1
unnamed: U69.5, U69.7
unnamed: R368.2, R372.1, U70.15 (INT)
unnamed: R371.2, R373.1, U70.17 (P1B0)
unnamed: U69.3, U71.9 (A6)
PNET1: C247.1, C250.1, C252.1, R361.2, R362.2, R367.1, U67.20 (VCC), U68.57 (VCC), U69.8 (VCC), U71.1 (VCCA), U71.2 (DIR); also elsewhere on the board
PNET3: C246.1 (+), D51.2 (K), Q39.2 (C), R363.2, R364.2, R365.2, R366.2, R369.2, R370.2, R372.2, R373.2, R374.2, U70.1 (VADC), U70.28 (VDD)
PNET5: Q39.1 (E), U71.24 (VCCB); also elsewhere on the board
Pluto_ESS_AEN: U69.2; also elsewhere on the board
SA2: U68.7 (A0); also elsewhere on the board
SD0: U68.3 (DQ0); also elsewhere on the board
SD1: U68.2 (DQ1); also elsewhere on the board
SD2: U68.1 (DQ2); also elsewhere on the board
SD3: U68.64 (DQ3); also elsewhere on the board
SD4: U68.63 (DQ4); also elsewhere on the board
SD5: U68.62 (DQ5); also elsewhere on the board
SD6: U68.61 (DQ6); also elsewhere on the board
SD7: U68.60 (DQ7); also elsewhere on the board
U8_1A3_KB_TP139: U67.6 (I2a); also elsewhere on the board
U8_2A1_KB_RXD: U67.11 (I0b); also elsewhere on the board
YMF_RD#_Buf: U71.18 (B4); also elsewhere on the board
YMF_WR#_Buf: U71.17 (B5); also elsewhere on the board

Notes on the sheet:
Device_Address_BUS
Device_Data_BUS
